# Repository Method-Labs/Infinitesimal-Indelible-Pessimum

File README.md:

# Infinitesimal Indelible Pessimum
  This is our first rocket. Our small, unforgettable starting point. Our objectives for it are as follows.
  - Create a small model rocket motor which has a flat thrust curve.
  - Create a rocket which uses this motor to reach 1km in height.
  - Use a flight computer to log data throughout the flight.

  The idea behind this rocket is begin to understand the fundementals of model rocketry, and move on to greater and better things with a strong knowledge base.

## Specifications
  The current specifications are as follows:
  - D Class Rocket Motor
    * 7 x 2.2cm
    * Ammonium Perchlorate and Aluminum Powder Propellant
    * Cylindrical Block Grain Geometry
    * Built-In Nozzle
  - Flight computer
    * STM32F103C8T7 MCU
    * BMP280 Barometer
    * MPU6050 IMU
    * W25Q32FV Memory Chip
    * 1 Pyro Channel
  - Construction Paper Body
  - 20cm Parachute

## Other Parameters
  - Stability > 0.5
  - Burn Time > 1 sec
  - 10ns < Total Impulse < 20ns

## Target Performance
  Targeted performance numbers are as follows:
  - Over 1000 m apogee.
  - Over 200 m/s top speed.

## Milestones
  We have set a few milestones to complete throughout this project in order to ensure proper conduct and a higher chance of success:
  1. Finalize rocket motor design.
  2. Finalize rocket design.
  3. Complete flight computer program.
  4. Complete testing of prototype flight computer.
    * This flight computer will have all the capabilities of the full flight-article flight computer, but will be built with breakout boards and solderless breadboards as opposed to a PCB. It is meant to test the capabilities of a flight computer while not requiring the investment both in terms of time and money that a full flight-ready computer will require.
  5. Complete recovery system deployment testing and validation. The testing procedure will be as follows:
    1. For tests 1-5, the recovery system will be independently tested on the ground with only the flight computer hooked up. There nust be an 80% or higher success rate to pass onto the final 5 tests.
      * Success Criteria: successful nosecone separation and parachute ejection.
    2. For tests 6-10, the recovery system will be integrated with the rest of the rocket, including the flight computer and a mass simulator substitute for the rocket motor. The mass simulator can be anything with roughly the same size and mass as the flight article rocket motor. The rocket will be dropped from a height of two stories (King's Academy Clock Tower is perfect for this). Tests 6 and 7 will not be parachute tests, where the parachute will be pre-deployed and the flight computer is inactive. While tests 8-10 will be full tests where the flight computer is active and responsible for deployment.
      * Success Criteria: successful deployment of recovery system and successful soft touchdown.
  6. Complete preliminary static fire tests with the rocket motor and no instrumentation. 1 nominal test is required before passing this milestone.
    * Success Criteria: The motor is intact throughout the test and burn time is near expected value within reason.
      * <5% Deviance: Nominal performance.
      * <10% Deviance: Acceptable performance, investigation should be undertaken but tests can continue as scheduled.
      * \>10% Deviance: Unacceptable performance, investiagtion should be undertaken and tests are to be suspended.
  7. Complete static fire tests with instrumentation and testing equipment.
    * Success Criteria: Motor thrust curve is as expected within reason. Test data will be run with regressional analysis in relation to the expected curve.
      * r > 0.9: Nominal performance.
      * r > 0.7: Acceptable performance, ivestigation should be undertaken but tests can continue as scheduled.
      * r < 0.7: Unacceptable performance, investagion should be undertakenand tests are to be suspended.
  
### Launch day
  Launch day is currently targeted NET Septeber 2019. Launch conditions are as follows:
  * Wind-speed <= 11 km/h.
  * Turbulence <= 10%.
  * 15C < Temperature < 40C

  Launch operations are as follows:
  * T - 1 hour: All equipment is on-site and ready to go.
  * T - 30 minutes: All equipment is set up and operational
  * T - 10 minutes: Ignition system is armed. Final systems check (go no-go procedure).
  * T - 5 minutes: Evacuate the launch area and a 10 meter circle around it. If exclusion zone is violated, countdown resets here.
  * T - 1 minute: Final countdown begins, all cameras rolling.
  * T - 2 seconds: Ignition.
  * T0: Liftoff.

  Recovery operations are as follows:
  * A set of binoculars are used to keep track of the rocket throughout the launch procedure.
  * At parachute deployment, the rocket's rough position will be clear, and the recovery team should begin moving towards it.
  * At touchdown, the recovery team should approach the landing site, but be 5 meters away from the rocket at the closest. They will be equipped with a fire extinguisher in case some unburned fule burns upon contact with the ground.
  * 2 minutes later, the recovery team tests rocket body temperature by touching it. If it's too high, they wait, otherwise, they can handle it and carry it back to the launchsite.

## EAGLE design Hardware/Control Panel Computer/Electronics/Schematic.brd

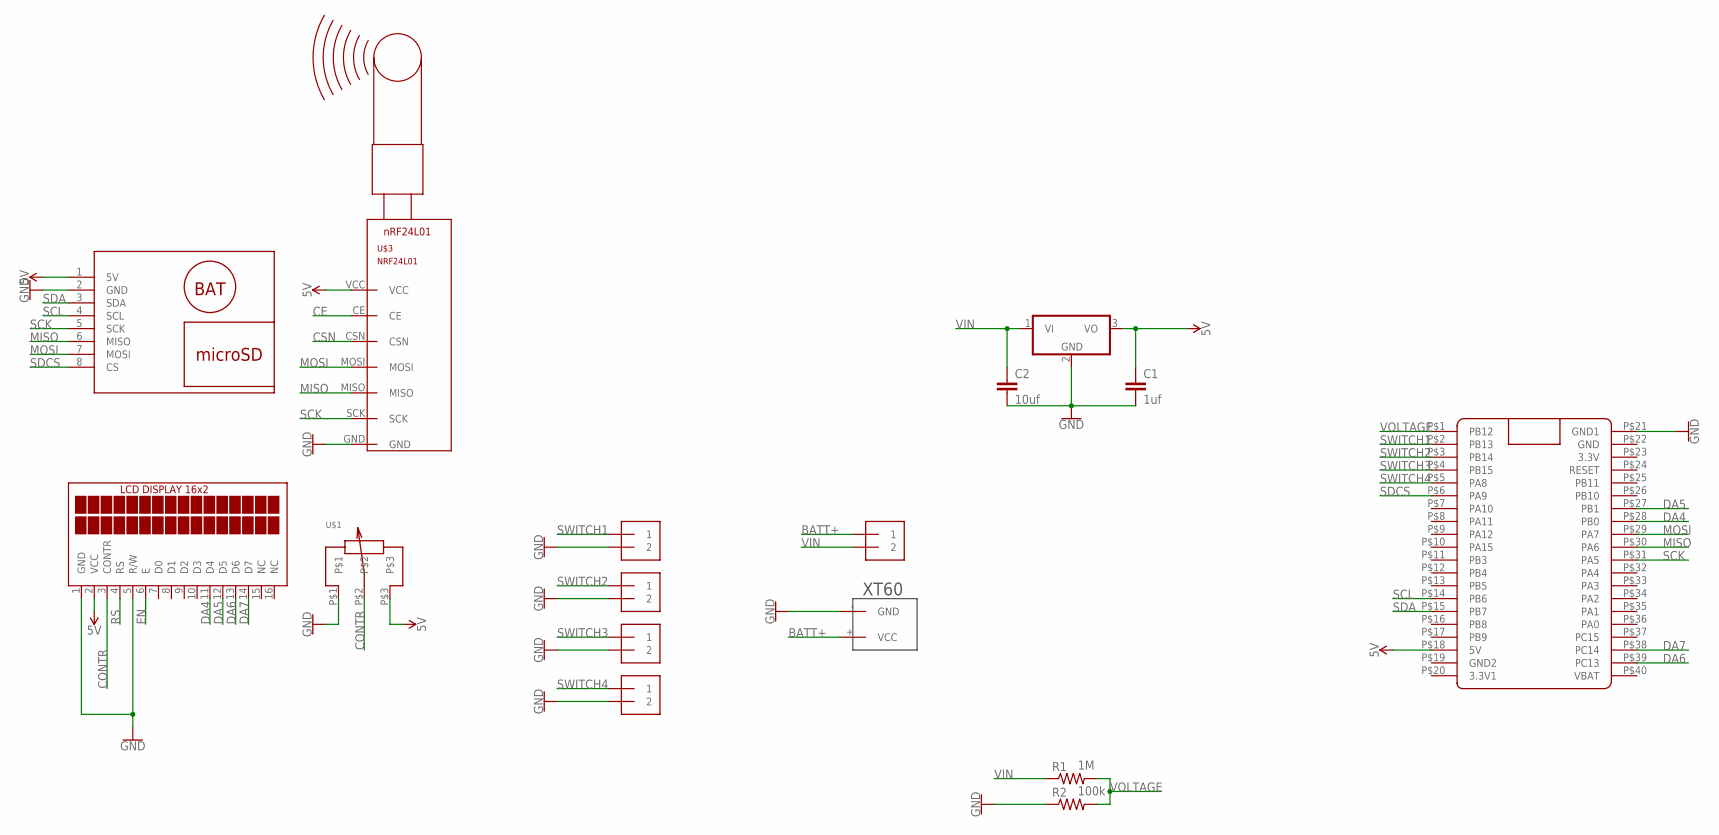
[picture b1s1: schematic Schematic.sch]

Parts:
C1: 1uf; C025-030X050
C2: 10uf; C025-030X050
DIS1: TUXGR_16X2_R2
IC1: 7805T; TO220H
J1, J2, J3, J4, J5: 1X2-3.5MM
R1: 1M; 0204/5
R2: 100k; 0204/5
U$1: POTENTIOMETER
U$2: XT60
U$3: NRF24L01
U$4: DATA-LOGGER-MINI
U$6: BLUE_PILL

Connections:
5V: C1.1, DIS1.2 (VCC), IC1.3 (VO), U$1.P$3, U$3.VCC, U$4.1 (5V), U$6.P$18 (5V)
BATT+: J5.1, U$2.+ (VCC)
CE: U$3.CE
CONTR: DIS1.3 (CONTR), U$1.P$2
CSN: U$3.CSN
DA4: DIS1.11 (D4), U$6.P$28 (PB0)
DA5: DIS1.12 (D5), U$6.P$27 (PB1)
DA6: DIS1.13 (D6), U$6.P$39 (PC13)
DA7: DIS1.14 (D7), U$6.P$38 (PC14)
EN: DIS1.6 (E)
GND: C1.2, C2.2, DIS1.1 (GND), DIS1.5 (R/W), IC1.2 (GND), J1.2, J2.2, J3.2, J4.2, R2.1, U$1.P$1, U$2.- (GND), U$3.GND, U$4.2 (GND), U$6.P$21 (GND1)
MISO: U$3.MISO, U$4.6 (MISO), U$6.P$30 (PA6)
MOSI: U$3.MOSI, U$4.7 (MOSI), U$6.P$29 (PA7)
RS: DIS1.4 (RS)
SCK: U$3.SCK, U$4.5 (SCK), U$6.P$31 (PA5)
SCL: U$4.4 (SCL), U$6.P$14 (PB6)
SDA: U$4.3 (SDA), U$6.P$15 (PB7)
SDCS: U$4.8 (CS), U$6.P$6 (PA9)
SWITCH1: J1.1, U$6.P$2 (PB13)
SWITCH2: J2.1, U$6.P$3 (PB14)
SWITCH3: J3.1, U$6.P$4 (PB15)
SWITCH4: J4.1, U$6.P$5 (PA8)
VIN: C2.1, IC1.1 (VI), J5.2, R1.1
VOLTAGE: R1.2, R2.2, U$6.P$1 (PB12)

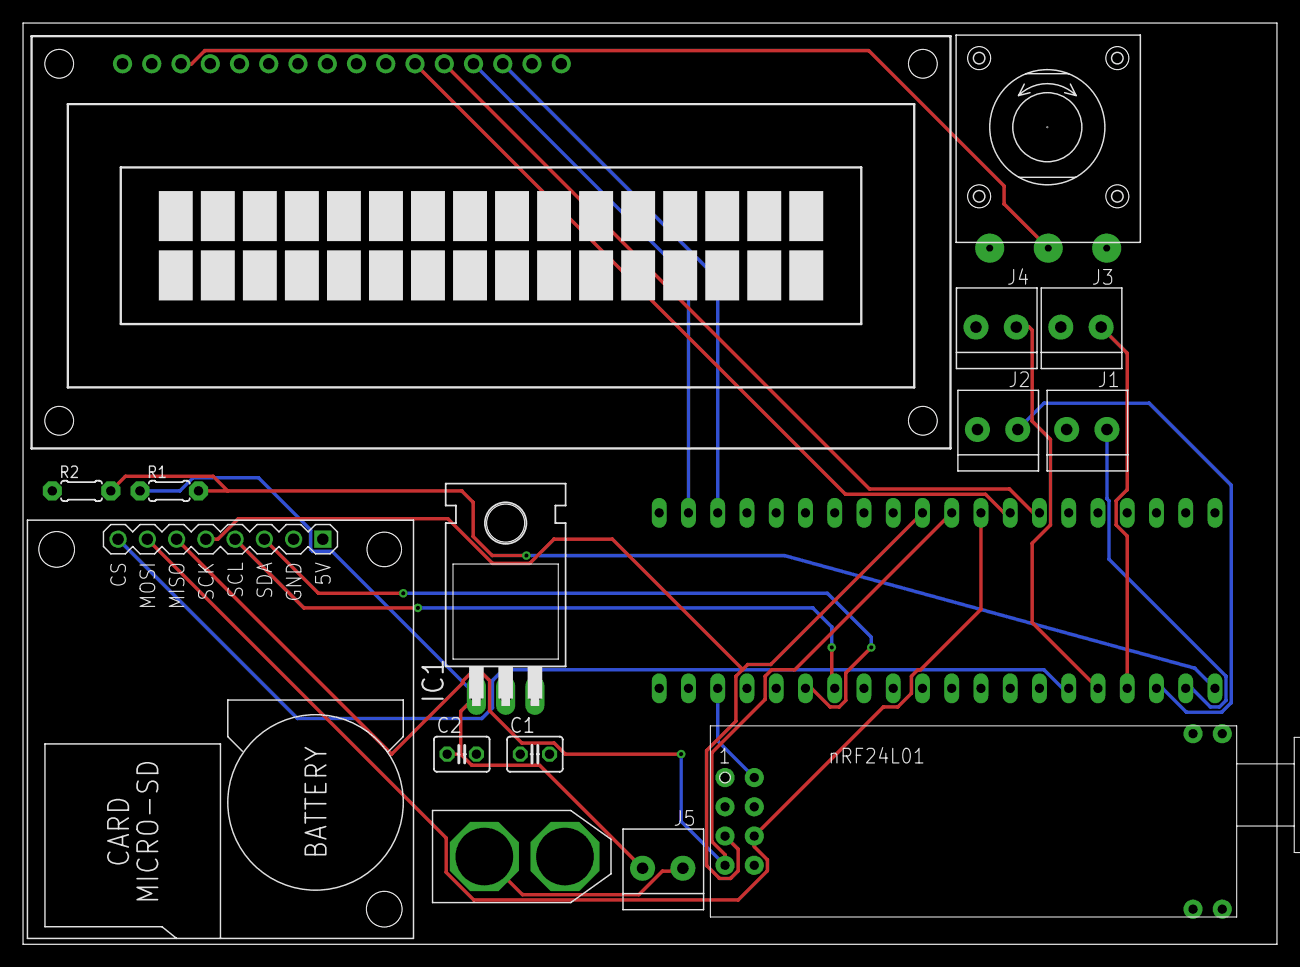
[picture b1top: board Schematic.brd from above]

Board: 2 copper layers, 108.9 x 80.0 mm, 16 parts (1 on the bottom side), 20 nets.

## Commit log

2019-05-24 Wrote README
2019-05-24 Write README
2019-05-24 Add OpenRocket file and Milestones to README.md
2019-05-24 Complete Flight Computer Prototpye
2019-05-24 Complete Prototype PCB
2019-05-27 Remove unnecessary files
2019-05-27 Add dependencies as submodules
2019-05-27 Add basic rocket motor specs
2019-05-29 Update rocket specs
2019-05-29 add flight computer prototype code
2019-05-30 Write flight computer prototype code
2019-05-31 Add calibration code and flight files
2019-05-31 Add .gitignore file
2019-05-31 Complete countdown and calibrator objects
2019-06-07 Change flight computer MCU in README
2019-06-07 Add materials list
2019-06-25 Complete OpenRocket design
2019-07-15 Enlarge rocket diameter and add shock cord
2019-07-21 More rocket design changes
2019-07-21 Add flight computer schematic
2019-07-22 Wire voltage regulation and switch circuits and add most nessecary components
2019-07-22 wire all components in flight computer schematics
2019-07-23 Change MCU to STM32F103C8T7
2019-07-23 Added custom MPU Eagle Library
2019-07-24 Added W25Q32FV Memory Chip through SPI Protocol
2019-07-24 Update README.md
    Updated MCU, motor and parachute dimensions and memory storage medium
2019-07-24 added more EAGLE Libraries
2019-07-24 add even more libraries
2019-07-24 completed bootloader circuit
2019-07-26 completed IMU breakout circuit
2019-08-24 added testing computer code
2019-08-28 Complete Control Panel Computer schematic
2019-09-15 remove 7-seg displays and complete board design
2019-09-20 add text to control panel computer PCB
2019-09-21 change control panel processor to STM32 Bluepill
2019-09-21 fix errors
2019-10-08 Completed preliminary motor draft

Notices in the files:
parts and their libraries:
MicroSD-Breakout: Released under the Creative Commons Attribution 4.0 International License: http://creativecommons.org/licenses/by/4.0
SparkFun-PowerSymbols: Licensing: Creative Commons ShareAlike 4.0 International - https://creativecommons.org/licenses/by-sa/4.0
